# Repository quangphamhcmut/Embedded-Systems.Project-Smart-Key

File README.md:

<h3 align="center">
</br> 
Smart Key System
</h3>

&nbsp;

<p align="center">
Smart Key system is a project for Embedded Systems course at HCMUT that aims to be a affordable solution to
bring some smart functions back to some old motorcycles. The system consist of 2 subsystems according to a 
key and a lock respectively.
</p>

&nbsp;

## 📝 Specification

### 💻 System requirement

[Requirement table](https://docs.google.com/spreadsheets/d/1nUn6pa3cHQUdWSz3ERi9wC6BmqBU7rnba5peyX5WJQM/edit?usp=sharing) 

### 🧩 Components

- This project requires below coponents:

| Components | Quantity | Feature |
| ---------- | :------: | ------- |
| `nRF24L01+` RF module | 2 | <ul> <li> Work at 2.4 GHz frequency </li> <li> Communicate with MCU via SPI protocol </li> <li> Auto acknowlegdenment when transmitting </li> <li> Controlable transmitting power </li>  <li> Great range </li> <li> Wide operating voltage </li> <li> Ultra low power down consumption </li> </ul> |
| `ATMEGA328P` MCU | 2 | <ul> <li> Wide availibility </li> <li> Support several communication protocol: UART, SPI, I2C </li> <li> Have a good amount of GPIO pin (2 pins for buttons, 3 pins for indicating LEDs, and 6 pins for comminucation with RF module) </li> <li> Have lots of documentation and a large community </li> <li> Simple to configure and program </li> <li> Ultra low power consumption </li> <li> Operate under a wide voltage range </li> |
| `CR2450` battery | 1 | <ul> <li> Small size </li> <li> Geat voltage consistency (3V) </li> <li> Discharge voltage of 2V </li> <li> Good capacity of 600 mAh </li> </ul> |
| Push button | 2 | <ul> <li> Alway off push button </li> </ul> |
| Relay | 2 | <ul> <li> Able to handle high power </li> </ul> |
| RGB LED | 2 | <ul> <li> Simple to implement and program </li> <li> Wide available </li> </ul> |

Others electric components like resistors, conductors, capacitors, etc would be added later
at the end of this project.

- 🔑 **Smart Key** requirement list:

| Components | Quantity | Function |
| ------------- | :-------------: | ------------- |
| `nRF24L01+` RF module | 1 | RF transmiting and receiving |
| Push button | 2 | One for locating the vehicle (flashing light, horn) and one for locking the vehicle |
| `CR2450` battery | 1 | Power supplying |
| `ATMEGA328P` MCU | 1 | Controlling|

- 🔒 **Smart Lock** requirement list:

| Components | Quantity | Function |
| ------------- | :-------------: | ------------- |
| `nRF24L01+` RF module | 1 | RF transmitting and receiving |
| Multicolor LEDs | 1 | Indicating device working mode |
| Relay | 2 | One for controlling the vehicle's power and one for vehicle's light |
| `ATMEGA328P` MCU | 1 | Controlling |

### 🔲 Block diagram

&nbsp;

## 💁 Our members

|     | Names | IDs |
| ------------- | -------------- | -------------- |
| 1 | Luong Thanh Vy | 2151280 |
| 2 | Nguyen Cuong Quoc | 2251045 |
| 3 | Pham Tan Quang | 2151248 |

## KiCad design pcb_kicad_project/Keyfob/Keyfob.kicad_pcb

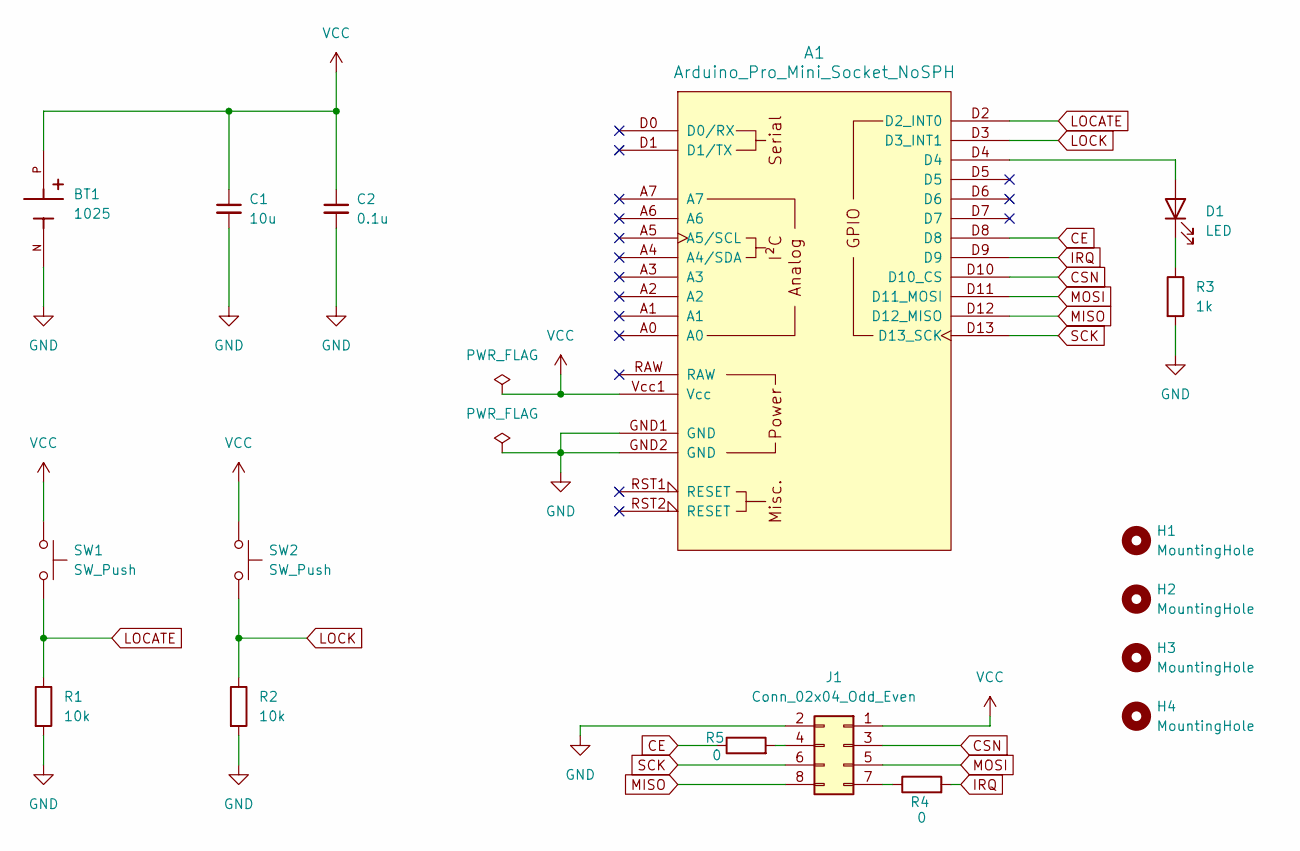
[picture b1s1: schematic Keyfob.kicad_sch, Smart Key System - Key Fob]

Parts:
A1: Arduino_Pro_Mini_Socket_NoSPH
BT1: 1025; BAT_1025; PARTREV H
C1: 10u; CP_Radial_D4.0mm_P2.00mm
C2: 0.1u; CP_Radial_D4.0mm_P2.00mm
D1: LED; LED_D3.0mm
H1, H2, H3, H4: MountingHole; MountingHole_3.2mm_M3
J1: Conn_02x04_Odd_Even; PinSocket_2x04_P2.54mm_Vertical
R1, R2: 10k; R_Axial_DIN0207_L6.3mm_D2.5mm_P10.16mm_Horizontal
R3: 1k; R_Axial_DIN0207_L6.3mm_D2.5mm_P10.16mm_Horizontal
R4, R5: 0; R_Axial_DIN0207_L6.3mm_D2.5mm_P10.16mm_Horizontal
SW1, SW2: SW_Push; SW_PUSH_6mm

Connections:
CE: A1.D8, R5.1
CSN: A1.D10 (D10_CS), J1.3
GND: A1.GND1 (GND), A1.GND2 (GND), BT1.N, C1.2, C2.2, J1.2, R1.2, R2.2, R3.2
IRQ: A1.D9, R4.2
LOCATE: A1.D2 (D2_INT0), R1.1, SW1.2
LOCK: A1.D3 (D3_INT1), R2.1, SW2.2
MISO: A1.D12 (D12_MISO), J1.8
MOSI: A1.D11 (D11_MOSI), J1.5
unnamed: A1.D4, D1.2 (A)
unnamed: D1.1 (K), R3.1
unnamed: J1.4, R5.2
unnamed: J1.7, R4.1
SCK: A1.D13 (D13_SCK), J1.6
VCC: A1.Vcc1 (Vcc), BT1.P, C1.1, C2.1, J1.1, SW1.1, SW2.1

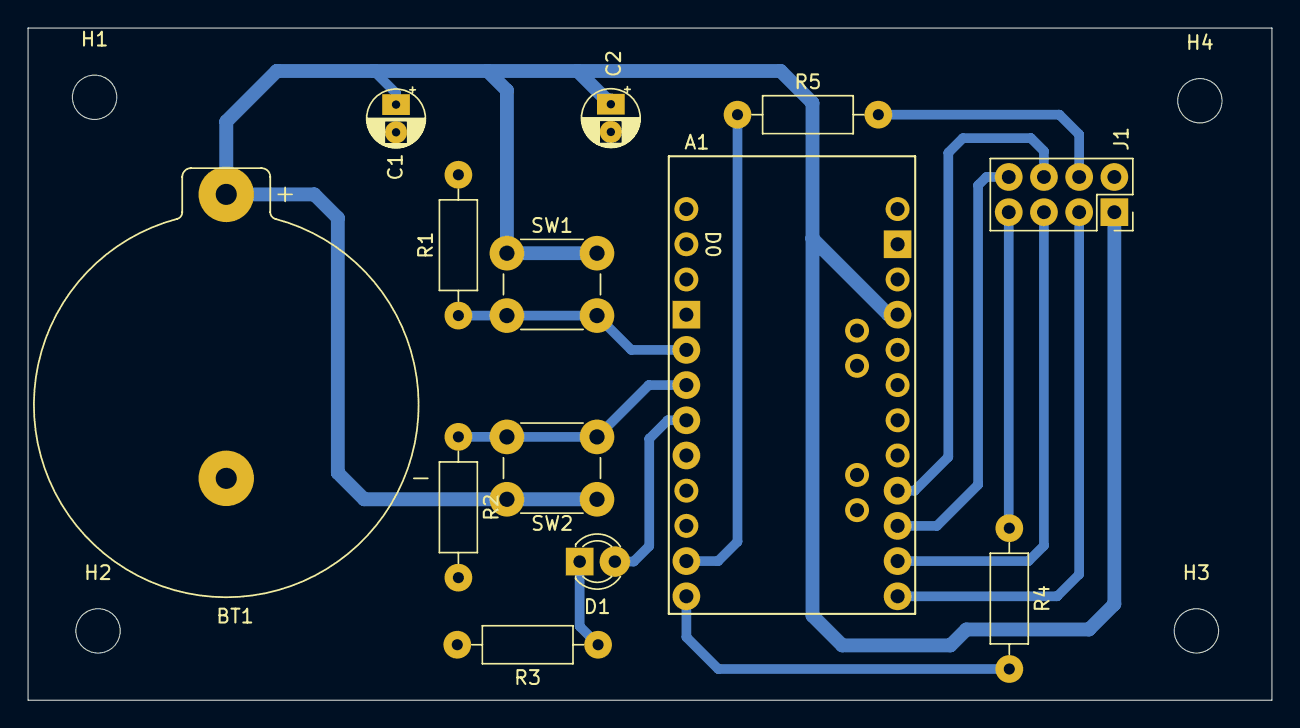
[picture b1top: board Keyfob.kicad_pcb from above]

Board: 2 copper layers, 89.7 x 48.5 mm, 17 parts (0 on the bottom side), 14 nets.

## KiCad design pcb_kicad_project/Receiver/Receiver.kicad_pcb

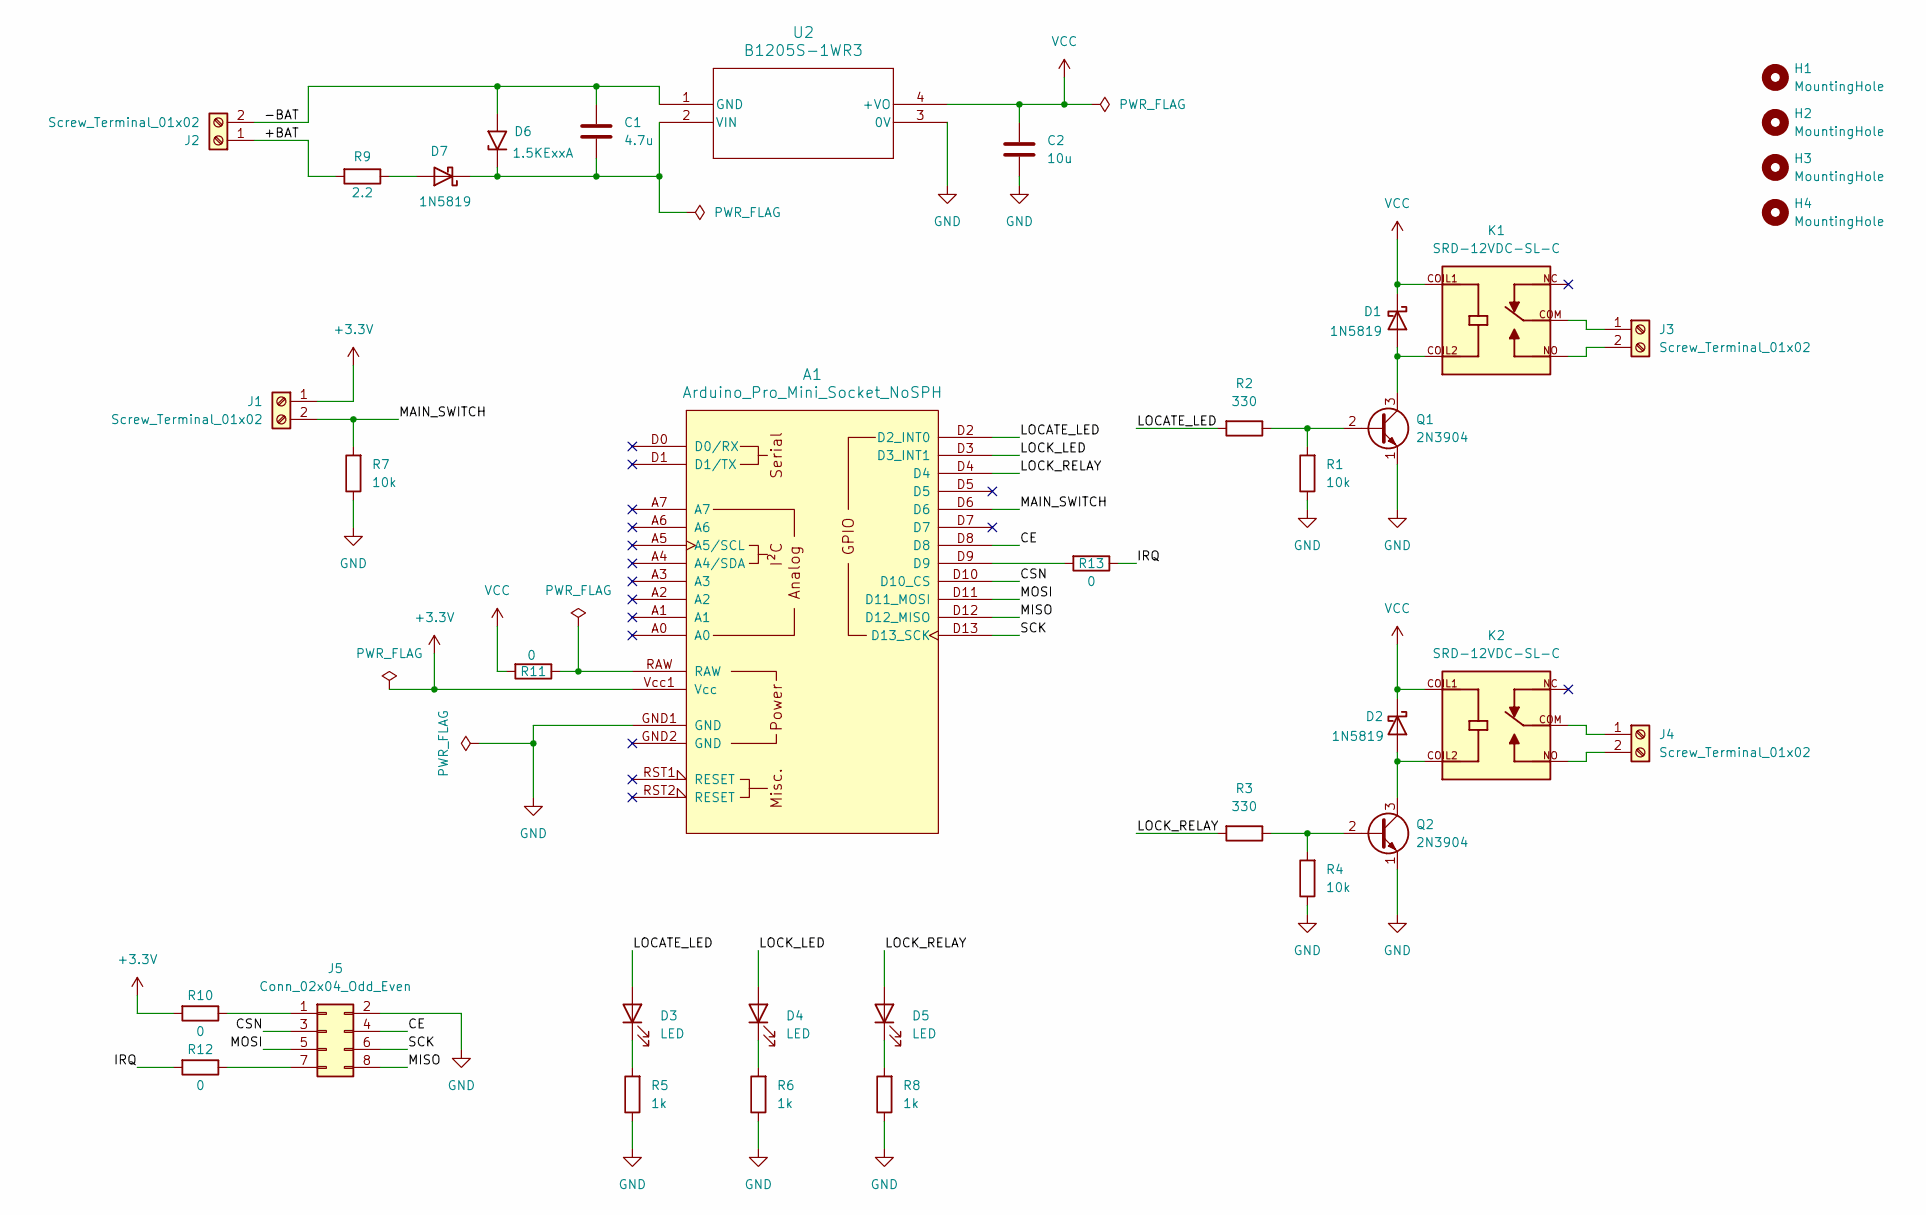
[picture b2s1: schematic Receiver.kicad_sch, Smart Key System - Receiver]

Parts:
A1: Arduino_Pro_Mini_Socket_NoSPH
C1: 4.7u; CP_Radial_D4.0mm_P2.00mm
C2: 10u; CP_Radial_D4.0mm_P2.00mm
D1, D2, D7: 1N5819; D_DO-41_SOD81_P10.16mm_Horizontal
D3, D4, D5: LED; LED_D3.0mm
D6: 1.5KExxA; D_DO-201AE_P15.24mm_Horizontal
H1, H2, H3, H4: MountingHole; MountingHole_3.2mm_M3
J1, J2, J3, J4: Screw_Terminal_01x02; TerminalBlock_CUI_TB007-508-02_1x02_P5.08mm_Horizontal
J5: Conn_02x04_Odd_Even; PinSocket_2x04_P2.54mm_Vertical
K1, K2: SRD-12VDC-SL-C; RELAY_SRD-12VDC-SL-C; PARTREV 1.0
Q1, Q2: 2N3904; TO-92_Inline
R1, R4, R7: 10k; R_Axial_DIN0207_L6.3mm_D2.5mm_P10.16mm_Horizontal
R2, R3: 330; R_Axial_DIN0207_L6.3mm_D2.5mm_P10.16mm_Horizontal
R5, R6, R8: 1k; R_Axial_DIN0207_L6.3mm_D2.5mm_P10.16mm_Horizontal
R9: 2.2; R_Axial_Power_L20.0mm_W6.4mm_P25.40mm
R10, R12, R13: 0; R_Axial_DIN0207_L6.3mm_D2.5mm_P10.16mm_Horizontal
R11: 0; R_Axial_DIN0207_L6.3mm_D2.5mm_P15.24mm_Horizontal
U2: B1205S-1WR3; SIP4_B_S-1WR3_MNS

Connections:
+3.3V: A1.Vcc1 (Vcc), J1.1, R10.2
/+BAT: J2.1, R9.2
/-BAT: C1.1, D6.2 (A2), J2.2, U2.1 (GND)
/CE: A1.D8, J5.4
/CSN: A1.D10 (D10_CS), J5.3
/IRQ: R12.2, R13.1
/LOCATE_LED: A1.D2 (D2_INT0), D3.2 (A), R2.2
/LOCK_LED: A1.D3 (D3_INT1), D4.2 (A)
/LOCK_RELAY: A1.D4, D5.2 (A), R3.2
/MAIN_SWITCH: A1.D6, J1.2, R7.2
/MISO: A1.D12 (D12_MISO), J5.8
/MOSI: A1.D11 (D11_MOSI), J5.5
/SCK: A1.D13 (D13_SCK), J5.6
GND: A1.GND1 (GND), C2.2, J5.2, Q1.1 (E), Q2.1 (E), R1.1, R4.1, R5.1, R6.1, R7.1, R8.1, U2.3 (0V)
unnamed: A1.D9, R13.2
unnamed: A1.RAW, R11.1
unnamed: D1.2 (A), K1.COIL2, Q1.3 (C)
unnamed: D2.2 (A), K2.COIL2, Q2.3 (C)
unnamed: D3.1 (K), R5.2
unnamed: D4.1 (K), R6.2
unnamed: D5.1 (K), R8.2
unnamed: C1.2, D6.1 (A1), D7.1 (K), U2.2 (VIN)
unnamed: D7.2 (A), R9.1
unnamed: J3.1, K1.COM
unnamed: J3.2, K1.NO
unnamed: J4.1, K2.COM
unnamed: J4.2, K2.NO
unnamed: J5.1, R10.1
unnamed: J5.7, R12.1
unnamed: Q1.2 (B), R1.2, R2.1
unnamed: Q2.2 (B), R3.1, R4.2
VCC: C2.1, D1.1 (K), D2.1 (K), K1.COIL1, K2.COIL1, R11.2, U2.4 (+VO)

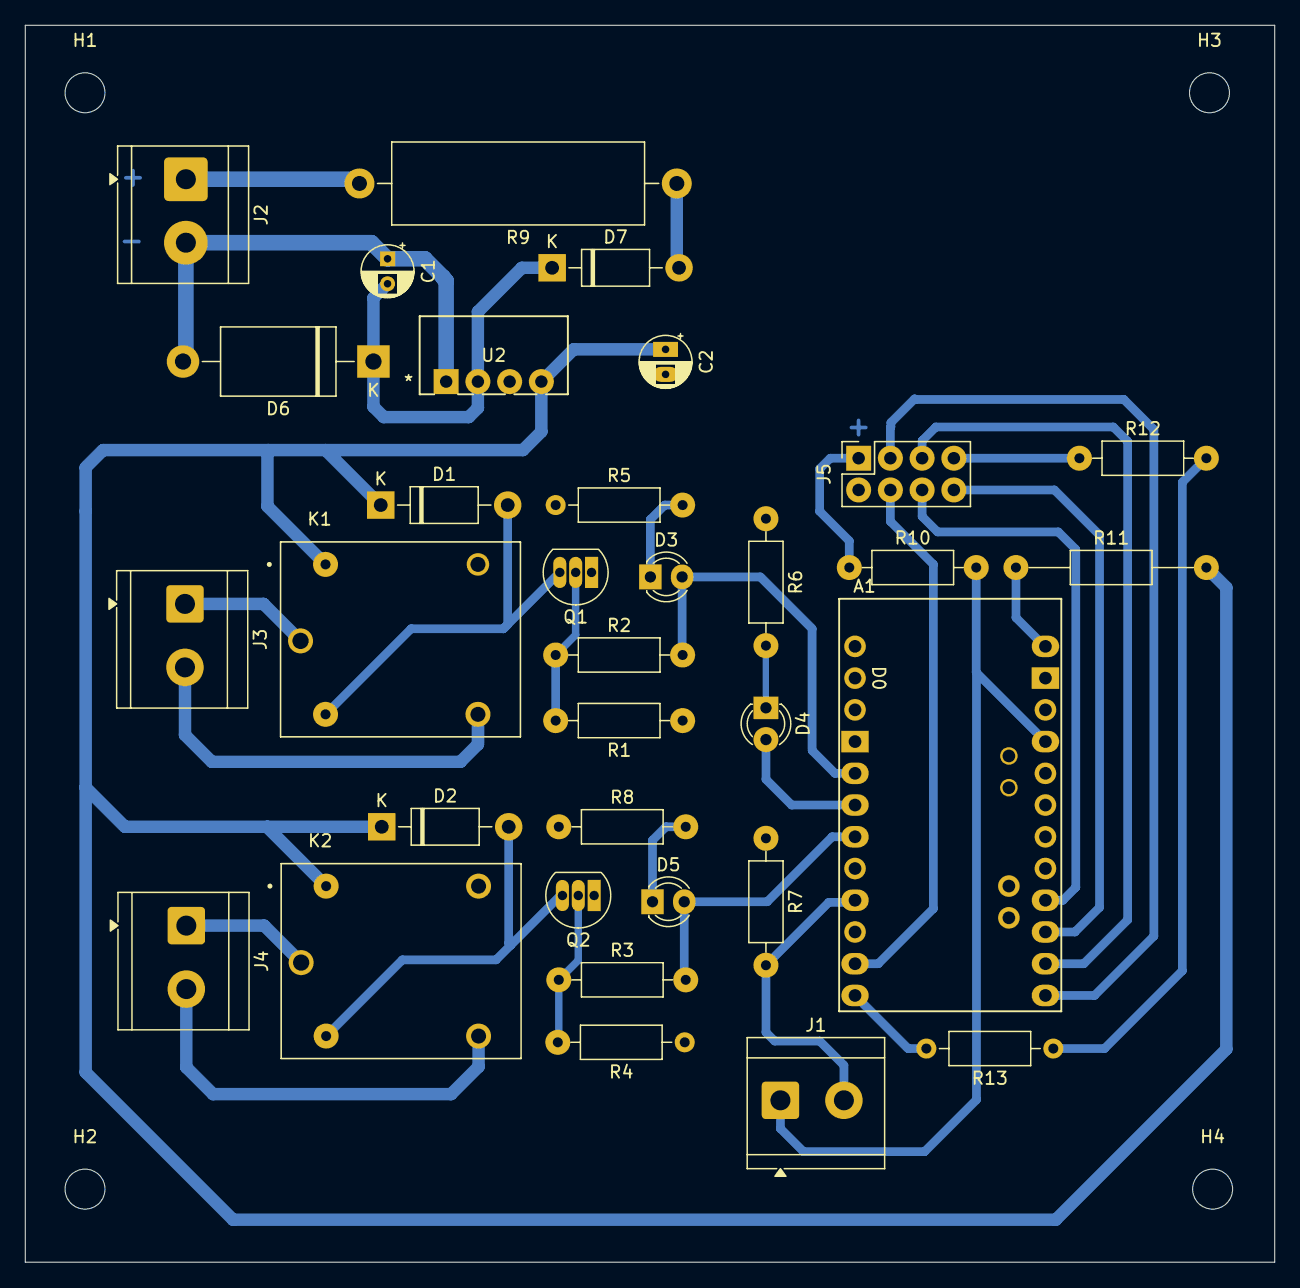
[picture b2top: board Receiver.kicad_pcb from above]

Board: 2 copper layers, 100.0 x 99.0 mm, 37 parts (0 on the bottom side), 32 nets.

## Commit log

2025-02-15 initial update
2025-02-15 update diagram
2025-02-15 update battery
2025-02-19 update test code
2025-03-04 add smartkey_system_schematic_rev1
2025-04-02 update project file
2025-04-02 update pcb project file
2025-04-02 update pcb project
2025-04-23 update code with library for keyfob
2025-04-24 update corecode vehicle
2025-05-05 update lock/unlock code
2025-05-05 update range limit and rolling code
2025-05-07 update README
    deleted: README.md
2025-05-07 add KiCAD PCB projects
2025-05-07 update schematic
2025-05-07 add reports
2025-05-07 update flowchart
